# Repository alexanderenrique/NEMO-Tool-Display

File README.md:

# NEMO Tool Display

IoT system with ESP32 displays that show real-time tool status from the NEMO backend system. Displays show who is using tools, usage duration, and tool operational status.

## Quick Start

### 1. VM Server Setup
```bash
cd vm-server
./setup.sh
```

The setup script will:
- Install and configure Mosquitto MQTT broker
- Set up Python virtual environment with dependencies
- Generate an HMAC key for NEMO↔broker authentication (broker only accepts signed messages when set)
- Start MQTT broker and NEMO server

### 2. ESP32 Configuration
Edit `display-firmware/src/config.h` with your WiFi SSID/password, MQTT broker and credentials, and tool name (e.g. `TARGET_TOOL_NAME`).

**⚠️ SECURITY WARNING:** Never commit real WiFi credentials, MQTT passwords, or IP addresses to version control!

### 3. Upload Firmware
```bash
cd display-firmware && pio run -t upload
```

## Hardware Connections

**TFT Display (480x320):**
```
ESP32 Pin  →  Display Pin
GPIO 23    →  MOSI
GPIO 18    →  SCLK
GPIO 5     →  CS
GPIO 17    →  DC
GPIO 16    →  RST
3.3V       →  VCC
GND        →  GND
```
T_IRQ
T_DO (Touch MISO) = 32
T_DIN = 26
T_CS = 33
T_CLK = 25
MISO
LED
SCK = 25
MOSI = 26
DC/RS = 27
RESET = 14
CS  = 13
GND
VCC

## Configuration

The system uses **centralized configuration** to ensure consistency between ESP32 and VM server:

### Centralized Configuration System
- **`display-firmware/src/config.h`** - Single configuration file (WiFi, MQTT, tool, display; not overridden by build flags)
- **`vm-server/config_parser.py`** - Python parser that reads from `display-firmware/src/config.h`
- **`NEMO_CONFIG_H`** (optional) - Absolute path to `config.h` when the firmware tree is not at `display-firmware/` beside `vm-server/`

### VM Server (config.env)
```env
# MQTT Configuration
MQTT_BROKER=your_mqtt_broker_ip   # Replace with your VM server's IP
MQTT_PORT=1886                    # NEMO backend port (VM server only)
MQTT_USERNAME=
MQTT_PASSWORD=

# Display Configuration
TIMEZONE_OFFSET_HOURS=-7
MAX_NAME_LENGTH=13
LOG_LEVEL=INFO
```

### ESP32 (display-firmware/src/config.h)
All ESP32 settings (WiFi, MQTT broker/port/credentials, tool ID/name, display) are in `display-firmware/src/config.h`. When broker authentication is enabled on the VM server, set `MQTT_USERNAME` and `MQTT_PASSWORD` in `display-firmware/src/config.h` to match `vm-server/config.env`.

### Port Configuration
- **ESP32 Port (1883)**: Used by ESP32 displays to receive status updates
- **NEMO Port (1886)**: Used by VM server to receive messages from NEMO backend
- **Configuration**: ESP32 port in `display-firmware/src/config.h`, NEMO port in `config.env`

Tool names are provided in MQTT messages from NEMO; no separate tool lookup or mapping file is required.

## MQTT Topics

**Backend Input (from NEMO):**
- `nemo/backend/tools/{tool_id}/status` - Individual tool status
- `nemo/backend/tools/overall` - Overall system status

**ESP32 Output (to displays):**
- `nemo/esp32/{tool_id}/status` - Tool status for specific display (uses tool ID for routing)
- `nemo/esp32/overall` - Overall status for all displays

**Server Status:**
- `nemo/server/status` - VM server health status

## Message Format

### Tool Status Message
```json
{
  "id": "113",
  "name": "woollam",
  "status": "active",
  "category": "Exfab",
  "operational": true,
  "problematic": false,
  "timestamp": "2025-01-15T10:30:00",
  "user": {
    "name": "John Doe",
    "username": "johndoe",
    "id": 80
  },
  "usage": {
    "start_time": "2025-01-15T10:30:00",
    "start_time_formatted": "Jan 15, 2025 at 10:30 AM",
    "usage_id": 12345
  }
}
```

### Overall Status Message
```json
{
  "total_tools": 199,
  "active_tools": 15,
  "available_tools": 180,
  "problematic_tools": 4,
  "timestamp": "2025-01-15T10:30:00"
}
```

### HMAC (NEMO↔broker)
When `MQTT_HMAC_KEY` is set in `config.env`, the VM server only accepts messages that include a valid HMAC. The broker (VM server) rejects any message without a correct signature. ESP32 traffic (port 1883) is not HMAC-protected.

**Envelope format when HMAC is enabled:** NEMO must publish:
```json
{"payload": "<original payload string>", "hmac": "<hex signature>", "algo": "sha256"}
```
- **payload**: The exact original payload string (e.g. JSON as a string). This is the string that was signed—same formatting/whitespace, no re-serialization.
- **hmac**: HMAC of that payload string, hex-encoded. Computed as `HMAC(secret_key, payload)` with key = shared secret (UTF-8), message = payload string (UTF-8), algorithm from `algo`.
- **algo**: Digest algorithm, e.g. `sha256` (default if omitted).

Verification uses the same secret (UTF-8), hashes the `payload` string as-is (UTF-8), and compares the hex digest with `hmac` using constant-time comparison. If HMAC is not required, leave `MQTT_HMAC_KEY` empty; then the server accepts normal (unwrapped) payloads.

## Setup Process Details

### VM Server Setup Steps
1. **Configuration Validation** - Checks for required files
2. **Install Mosquitto** - MQTT broker installation
3. **Stop Existing Processes** - Clean shutdown of running services
4. **Clean Configuration** - Remove old config and log files
5. **Create Mosquitto Config** - Generate broker configuration
6. **Test Configuration** - Verify MQTT functionality
7. **Set Up Python Environment** - Create venv and install dependencies
8. **Generate Tool Mappings** - Fetch tools from NEMO API
9. **Set Up Environment File** - Create config.env and generate HMAC key
10. **Start MQTT Broker** - Launch Mosquitto
11. **Start NEMO Server** - Launch Python application

### ESP32 Setup Steps
1. **Configure WiFi** - Set SSID and password in `display-firmware/src/config.h`
2. **Configure MQTT** - Set broker IP and port in `display-firmware/src/config.h`
3. **Set Tool Name** - Specify which tool this display shows
4. **Upload Firmware** - Compile and flash to ESP32

## Troubleshooting

### ESP32 Issues
**Can't connect to WiFi:**
- Check WiFi credentials in `display-firmware/src/config.h`
- Verify network is 2.4GHz (ESP32 doesn't support 5GHz)
- Check signal strength

**Can't connect to MQTT:**
- Verify MQTT broker IP address in `display-firmware/src/config.h`
- Check MQTT port (1883 for ESP32, 1886 for NEMO backend)
- Ensure ESP32 and server are on same network
- Check MQTT broker IP and port match the server

**Display not working:**
- Check wiring connections (see Hardware Connections)
- Verify TFT_eSPI library is installed
- Monitor serial output: `pio device monitor`

### VM Server Issues
**MQTT broker won't start:**
- Check logs: `tail -f vm-server/mqtt/log/mosquitto.log`
- Verify ports 1883 and 1886 are not in use
- Check Mosquitto configuration: `mosquitto -c mqtt/config/mosquitto.conf -v`

**NEMO server issues:**
- Check Python dependencies: `pip install -r requirements.txt`
- Verify configuration in `config.env`
- Run comprehensive tests: `python3 test_system.py`
- Test MQTT: `mosquitto_sub -h localhost -t "nemo/#" -v`

**NEMO backend MQTT "unauthorized" (rc=5) or connection timeout:**
- The NEMO Django app (nemo-ce-alex) must use the **same** broker, port, username, and password as `vm-server/config.env`. Set NEMO's MQTT settings to match: `MQTT_BROKER` (use the machine IP where Mosquitto runs, or `localhost` if NEMO and Mosquitto run on the same host), `MQTT_PORT=1886`, `MQTT_USERNAME` and `MQTT_PASSWORD` identical to config.env.
- **Unauthorized (rc=5)**: Username/password in NEMO do not match the broker's password file. Re-run `vm-server/setup.sh` to set broker auth, then copy the printed MQTT config into NEMO's MQTT settings.
- **Connection timeout to localhost:1886**: Mosquitto may not be running, or NEMO is pointing at the wrong host. Start the broker (e.g. `vm-server/quick_restart.sh` or start Mosquitto manually) and ensure NEMO's broker host is correct. When VM server or mqtt_monitor starts, they print the current MQTT config for verification.

### Network Issues
**ESP32 can't reach server:**
- Ensure both devices are on same network
- Check firewall settings on VM server
- Verify MQTT broker is listening on correct interface
- Test with: `mosquitto_pub -h SERVER_IP -t "test" -m "hello"`

## Monitoring and Debugging

### Available Scripts

#### Setup Script (`setup.sh`)
Complete system setup and configuration:
```bash
cd vm-server
./setup.sh
```

**What it does:**
- Installs Mosquitto MQTT broker
- Sets up Python virtual environment
- Creates MQTT configuration
- Starts all services

#### Quick Restart Script (`quick_restart.sh`)
Fast restart for development:
```bash
cd vm-server
./quick_restart.sh
```

**What it does:**
1. Stops all existing MQTT broker and server processes
2. Clears MQTT ports (1883, 1886)
3. Starts Mosquitto MQTT broker on both ports
4. Starts the NEMO server (vm-server/main.py)

#### Test Script (`test_system.py`)
Comprehensive system testing:
```bash
cd vm-server
python3 test_system.py
```

**What it tests:**
- System processes (MQTT broker, NEMO server)
- Port connectivity (1883, 1886)
- Message parsing and trimming logic
- MQTT connections (NEMO and ESP32)
- End-to-end functionality

#### MQTT Monitor (`mqtt_monitor.py`)
Real-time MQTT traffic monitoring:
```bash
cd vm-server
python3 mqtt_monitor.py
```

**Features:**
- Monitors MQTT ports (1883 and NEMO port from config)
- Shows message direction and content
- Displays connection status
- Real-time traffic analysis

**⚠️ Important - Internal Development Setup:**
When running the actual NEMO application and this display system on the same machine, restarting Mosquitto will temporarily break NEMO's MQTT connection:

1. **During restart:** NEMO's connection to Mosquitto is severed
2. **Message impact:** Messages published during the restart may be lost or queued
3. **Reconnection:** NEMO's MQTT plugin typically auto-reconnects once Mosquitto is back up

**Best Practice:** Avoid restarting Mosquitto during active tool usage. For production deployments, run the MQTT broker on a separate machine to prevent this issue.

### MQTT Monitoring
```bash
# Monitor all NEMO topics
mosquitto_sub -h localhost -t "nemo/#" -v

# Monitor specific tool
mosquitto_sub -h localhost -t "nemo/esp32/woollam/status" -v

# Monitor server status
mosquitto_sub -h localhost -t "nemo/server/status" -v

# Use the comprehensive monitor script
cd vm-server
python3 mqtt_monitor.py
```

### Log Files
- **MQTT Broker:** `vm-server/mqtt/log/mosquitto.log`
- **NEMO Server:** Console output or `nemo_server.log`
- **ESP32:** Serial monitor output

### Testing MQTT
```bash
# Publish test message
mosquitto_pub -h localhost -t "nemo/test" -m "test message"

# Subscribe to test
mosquitto_sub -h localhost -t "nemo/test" -v
```

## Project Structure

```
├── vm-server/                    # Python server and configuration
│   ├── main.py                  # Main NEMO server application
│   ├── setup.sh                 # Complete system setup script
│   ├── quick_restart.sh         # Fast restart for development
│   ├── test_system.py           # Comprehensive system tests
│   ├── mqtt_monitor.py          # MQTT traffic monitor
│   ├── config_parser.py         # Centralized config parser
│   ├── config.env              # Server configuration
│   ├── requirements.txt        # Python dependencies
│   ├── mqtt/                   # MQTT broker files
│   │   ├── config/mosquitto.conf
│   │   ├── data/               # Persistence data
│   │   └── log/                # Log files
│   └── venv/                   # Python virtual environment
├── display-firmware/               # PlatformIO / ESP32 firmware
│   ├── src/main.cpp            # ESP32 firmware
│   ├── src/config.h            # ESP32 configuration (single source)
│   ├── include/lv_conf.h        # LVGL configuration
│   ├── lib/                    # ESP32 libraries
│   └── platformio.ini           # Build configuration
├── tool-display-pcb/             # KiCad project, gerbers; backups/ holds zip snapshots
└── README.md                   # This file
```

## Security Notes

### 🔒 **CRITICAL SECURITY REQUIREMENTS**

1. **Never commit real credentials to version control:**
   - WiFi SSID and password in `display-firmware/src/config.h`
   - MQTT broker IP addresses
   - NEMO API tokens in `config.env`
   - Any other sensitive configuration

2. **Use environment variables or local config files:**
   - Keep `config.env` in `.gitignore` (already configured)
   - Use placeholder values in committed files
   - Set real values locally for development

3. **API Token Security:**
   - Keep your NEMO token secure and don't commit it to version control
   - Use strong, unique tokens
   - Rotate tokens regularly

4. **MQTT Security:**
   - HMAC is between the NEMO backend and the VM server (broker): when `MQTT_HMAC_KEY` is set, the server only accepts messages with a valid HMAC and rejects others.
   - NEMO sends: `{"payload": "<exact payload string>", "hmac": "<hex>", "algo": "sha256"}`. The signed value is the exact `payload` string (UTF-8); key is the shared secret (UTF-8). No re-serialization or trimming.
   - Restrict broker access with firewall rules

5. **Network Security:**
   - Use VPN or firewall rules to restrict access to MQTT broker
   - Consider using private networks for IoT devices
   - Monitor network traffic for anomalies

### 🛡️ **Security Checklist**
- [ ] All real credentials removed from committed files
- [ ] `config.env` is in `.gitignore` and not tracked
- [ ] Placeholder values used in example configurations
- [ ] MQTT broker secured with authentication (if needed)
- [ ] Network access restricted appropriately
- [ ] Regular security updates applied

## Contributing

1. Fork the repository
2. Create a feature branch
3. Make your changes
4. Test thoroughly
5. Submit a pull request

## License

[Add your license information here]

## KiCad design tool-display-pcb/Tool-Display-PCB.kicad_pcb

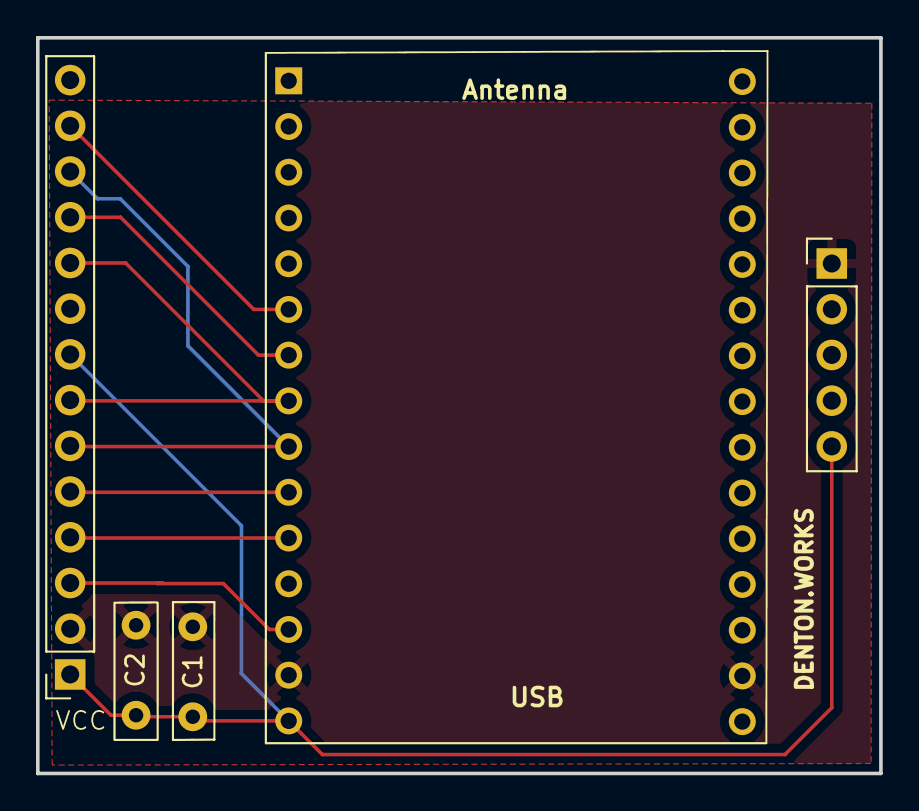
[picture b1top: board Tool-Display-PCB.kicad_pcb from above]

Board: 2 copper layers, 46.8 x 40.9 mm, 5 parts (0 on the bottom side), 9 nets.

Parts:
C1, C2: C_Small_US; C_Disc_D7.5mm_W4.4mm_P5.00mm
J1: 4" TFT SPI DISPLAY; TFT-14pin-Alex
J2: ESP32 30-Pin; ESP32-C3-30pin-Alex
J4: Conn_01x05_Pin; Alex-5pin-microUSB

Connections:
GND: C1.1, C2.1, J1.GND (Pin_2), J2.GND (Pin_2), J4.GND (Pin_1)
unnamed: C1.2, C2.2, J1.LED (Pin_8), J1.VCC (Pin_1), J2.VIN (3.3), J4.VIN (Pin_5)
unnamed: J1.CS (Pin_3), J2.13 (Pin_3)
unnamed: J1.RST (Pin_4), J2.14 (Pin_5)
unnamed: J1.DC (Pin_5), J2.27 (Pin_6)
unnamed: J1.SCK (Pin_7), J1.T_CLK (Pin_10), J2.25 (Pin_8)
unnamed: J1.MOSI (Pin_6), J1.T_DIN (Pin_12), J2.26 (Pin_7)
unnamed: J1.T_CS, J2.33 (Pin_9)
unnamed: J1.T_DO, J2.32 (Pin_10)

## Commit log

2025-09-04 test
2025-09-04 created the whole structure of the project
2025-09-04 working through the API, filtering
2025-09-05 added a few api test functions
2025-09-05 changed from API to MQTT polling
2025-09-18 vm broker config, tool specific publication
2025-09-19 created a set up, got the basic UI working
2025-09-19 comprehensive setup and start script, SSL actually working
2025-09-19 everything is working, good checkpoint
2025-09-19 cleaned shell scripts, UI changes
2025-09-21 working UI, dynamic VM IP detection
2025-09-21 Add white background/black text UI, dynamic IP setup, and ESP32 improvements
    - Updated ESP32 display to white background with black text for better readability
    - Added configurable color variables in create_simple_ui() function
    - Implemented dynamic IP detection and configuration for VM server
    - Added first/last name display support in MQTT messages
    - Created dynamic IP setup scripts and documentation
    - Fixed platformio.ini configuration for proper LVGL compilation
2025-09-21 added tool mapping function, good check point
2025-09-21 check point
2025-09-21 checkpoint, about to do some clean up
2025-09-21 cleaned it up, created a tool mapping script
2025-09-21 Remove config.env from tracking and add to .gitignore
    - Remove vm_server/config.env from git tracking to protect NEMO token
    - Add config.env to .gitignore to prevent future commits
    - Keep config.env.example for reference
2025-09-29 created check and start shell script
2025-10-14 working version, centralized config, debugged esp port 1883
2025-10-14 cleaned and consolidated testing and start scripts
2025-10-16 generates correct CA with the right parts
2025-10-20 Security: Remove platformio.ini from tracking and enhance security
    - Remove platformio.ini from git tracking to protect WiFi credentials
    - Add *.ini to .gitignore to prevent future commits of ini files
    - Update README.md with security warnings and best practices
    - Add comprehensive SECURITY.md guide
    - Fix hardcoded paths in mosquitto.conf to use relative paths
    - All sensitive credentials now use placeholders in committed files
2026-01-28 migration
2026-02-16 added ini file, hardware.h
2026-02-16 added hardware.h, config.h, it works
2026-02-17 updated main.py
2026-02-17 now using unique IDs for tools
2026-02-17 touch works
2026-02-18 changed downloaded tools
2026-02-18 updates to setup script dependedncies
2026-02-18 mqtt on vm is local host, set up changes
2026-02-18 mqtt on vm permissions issues
2026-02-18 checkpoint, waiting on IT
2026-02-18 PCB changes
2026-02-19 pcb finished, shipped
2026-02-24 test connection update, cleanup
2026-02-24 all the commits
2026-02-24 everything works, checkpoint
2026-02-24 changes to enable disable, cleaning unnescessary messages
2026-02-24 set up improvements
2026-02-24 correct IP address for CA cert generation
2026-02-25 password and HMAC working
2026-02-25 HMAC and admin working
2026-02-26 setup clean up for smoother launches
2026-02-26 ESP32 cleanup and reconcile
2026-02-27 working nicely
2026-03-01 chore: remove secrets from repo — add config.h.example and .env.example, gitignore config.h
    Made-with: Cursor
2026-03-01 chore: stop tracking secrets and sensitive files
    - Add .gitignore: .cache/, vm_server/mqtt/certs/, vm_server/mqtt/config/passwd,
    vm_server/mqtt/config/mosquitto.conf, vm_server/mqtt/data/, vm_server/mqtt/log/
    - Add mosquitto.conf.example and passwd.example (safe templates)
    - Sanitize config.env.example (placeholder credentials)
    - Remove from tracking: clangd cache, TLS certs/keys, MQTT passwd, local
    mosquitto.conf, mosquitto.db
2026-03-01 cleaned up, no more websocket
2026-03-01 UI change, tool status border instead of box
2026-03-02 added display code folder
2026-03-02 gitignore
2026-03-03 server cashing because of missing config fixed
2026-03-03 updates to bash scripts
2026-03-03 sudo and mosquitto
2026-03-16 checkpoint
2026-03-16 beta for operational and task pipeline
2026-03-18 pretty good check point
2026-03-18 better checkpoint
2026-03-18 looking good checkpoint
2026-03-18 so sexy, so happy
2026-03-19 the latest
2026-03-19 test changes
2026-03-19 monitor cleanup
2026-03-24 improved vm code
2026-03-24 monitor
2026-03-24 ahhhhhh
2026-03-24 jesus save me
2026-03-24 faster setup
2026-03-25 added systemd
2026-03-25 better monitor
2026-03-25 broken pipe
2026-03-25 systemd
2026-03-26 logging for flaky messages
2026-04-07 1886 connection script
2026-04-07 1886 connection script improvements
2026-04-08 is this working
2026-04-09 tool naming, max user name length, mysterious state bug
2026-04-10 added scripts
2026-04-10 server set up
2026-04-10 server
2026-04-10 simplifying dmanit
2026-04-10 not having fun
2026-04-10 working checkpoint, about to make clarity changes
2026-04-10 big refactor and polish
2026-04-23 UI changes, dynamic client ID
2026-04-23 PCB updates, narrower, additional USB option
2026-04-29 adding reservations
2026-04-30 UI changes
2026-04-30 reservartion UI changes
2026-05-04 formatting, ISO time, ASCII dashes
2026-05-06 small UI update
